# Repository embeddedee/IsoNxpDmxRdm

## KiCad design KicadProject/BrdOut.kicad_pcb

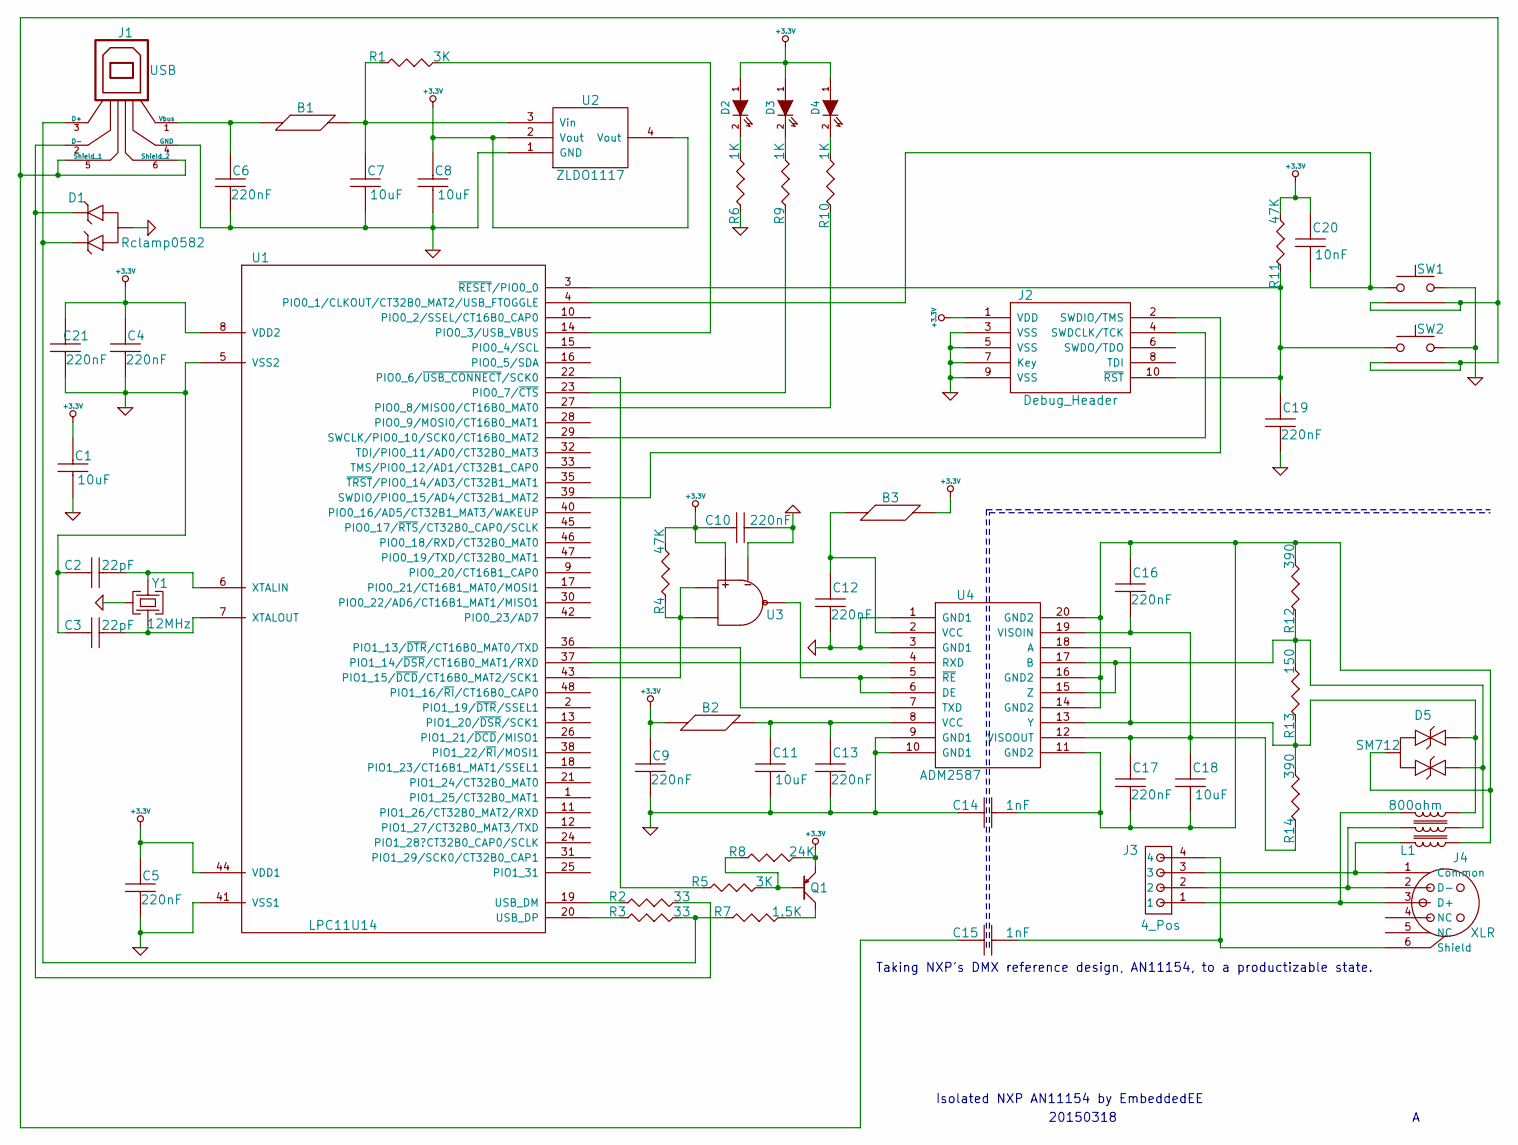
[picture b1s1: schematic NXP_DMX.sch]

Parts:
B1, B2, B3: Ferrite_Bead
C1, C7, C8, C11, C18: 10uF
C2, C3: 22pF
C4, C5, C6, C9, C10, C12, C13, C16, C17, C19, C21: 220nF
C14, C15: 1nF
C20: 10nF
D1: Rclamp0582
D2, D3, D4: LED
D5: SM712
J1: USB
J2: Debug_Header
J3: 4_Pos
J4: XLR
L1: 800ohm
Q1: BJT_PNP
R1, R5: 3K
R2, R3: 33
R4, R11: 47K
R6, R9, R10: 1K
R7: 1.5K
R8: 24K
R12, R14: 390
R13: 150
SW1, SW2: Button
U1: LPC11U14
U2: ZLDO1117
U3: 1G_NAND
U4: ADM2587
Y1: 12MHz

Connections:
+3.3V: B2.1 (B1), B3.2 (B2), C1.1 (C1), C4.1 (C1), C5.1 (C1), C8.1 (C1), C9.1 (C1), C10.1 (C1), C20.1 (C1), C21.1 (C1), D2.1 (A), D3.1 (A), D4.1 (A), J2.1 (VDD), Q1.2 (E), R4.2 (R2), R8.2 (R2), R11.2 (R2), U1.8 (VDD2), U1.44 (VDD1), U2.2 (Vout), U2.4 (Vout), U3.5 (Vcc)
GND: C1.2 (C2), C2.1 (C1), C3.1 (C1), C4.2 (C2), C5.2 (C2), C6.2 (C2), C7.2 (C2), C8.2 (C2), C9.2 (C2), C10.2 (C2), C11.2 (C2), C12.2 (C2), C13.2 (C2), C14.1 (C1), C19.2 (C2), C21.2 (C2), D1.3 (A), J1.4 (GND), J2.3 (VSS), J2.5 (VSS), J2.7 (Key), J2.9 (VSS), R6.1 (R1), SW1.2, SW2.2, U1.5 (VSS2), U1.41 (VSS1), U2.1 (GND), U3.3 (Vss), U4.1 (GND1), U4.3 (GND1), U4.9 (GND1), U4.10 (GND1), Y1.3 (Shield)
unnamed: B1.1 (B1), C6.1 (C1), J1.1 (Vbus)
unnamed: B1.2 (B2), C7.1 (C1), R1.1 (R1), U2.3 (Vin)
unnamed: B2.2 (B2), C11.1 (C1), C13.1 (C1), U4.8 (VCC)
unnamed: B3.1 (B1), C12.1 (C1), U4.2 (VCC)
unnamed: C2.2 (C2), U1.6 (XTALIN), Y1.1 (Y1)
unnamed: C3.2 (C2), U1.7 (XTALOUT), Y1.2 (Y2)
unnamed: C14.2 (C2), C16.1 (C1), C17.2 (C2), C18.2 (C2), D5.3 (A), L1.6, R12.2 (R2), U4.11 (GND2), U4.14 (GND2), U4.16 (GND2), U4.20 (GND2)
unnamed: C15.1 (C1), J1.5 (Shield_1), J1.6 (Shield_2), SW1.3, SW1.4, SW2.3, SW2.4
unnamed: C15.2 (C2), J3.4, J4.6 (Shield)
unnamed: C16.2 (C2), C17.1 (C1), C18.1 (C1), R14.1 (R1), U4.12 (VISOOUT), U4.19 (VISOIN)
unnamed: C19.1 (C1), J2.10 (~RST), R11.1 (R1), SW2.1, U1.3 (~RESET~/PIO0_0)
unnamed: C20.2 (C2), SW1.1, U1.4 (PIO0_1/CLKOUT/CT32B0_MAT2/USB_FTOGGLE)
unnamed: D1.1 (K1), J1.2 (D-), R2.2 (R2)
unnamed: D1.2 (K2), J1.3 (D+), R3.2 (R2), R7.1 (R1)
unnamed: D2.2 (K), R6.2 (R2)
unnamed: D3.2 (K), R9.2 (R2)
unnamed: D4.2 (K), R10.2 (R2)
unnamed: D5.1 (K1), L1.4, R13.1 (R1), R14.2 (R2), U4.13 (Y), U4.18 (A)
unnamed: D5.2 (K2), L1.5, R12.1 (R1), R13.2 (R2), U4.15 (Z), U4.17 (B)
unnamed: J2.2 (SWDIO/TMS), U1.39 (SWDIO/PIO0_15/AD4/CT32B1_MAT2)
unnamed: J2.4 (SWDCLK/TCK), U1.29 (SWCLK/PIO0_10/SCK0/CT16B0_MAT2)
unnamed: J3.1, J4.3 (D+), L1.3
unnamed: J3.2, J4.2 (D-), L1.2
unnamed: J3.3, J4.1 (Common), L1.1
unnamed: Q1.1 (B), R5.2 (R2), R8.1 (R1)
unnamed: Q1.3 (C), R7.2 (R2)
unnamed: R1.2 (R2), U1.14 (PIO0_3/USB_VBUS)
unnamed: R2.1 (R1), U1.19 (USB_DM)
unnamed: R3.1 (R1), U1.20 (USB_DP)
unnamed: R4.1 (R1), U1.43 (PIO1_15/~DCD~/CT16B0_MAT2/SCK1), U3.1 (In1), U3.2 (In2)
unnamed: R5.1 (R1), U1.22 (PIO0_6/~USB_CONNECT~/SCK0)
unnamed: R9.1 (R1), U1.23 (PIO0_7/~CTS)
unnamed: R10.1 (R1), U1.27 (PIO0_8/MISO0/CT16B0_MAT0)
unnamed: U1.36 (PIO1_13/~DTR~/CT16B0_MAT0/TXD), U4.7 (TXD)
unnamed: U1.37 (PIO1_14/~DSR~/CT16B0_MAT1/RXD), U4.4 (RXD)
unnamed: U3.4 (Out), U4.5 (~RE), U4.6 (DE)

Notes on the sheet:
20150318
Taking NXP's DMX reference design, AN11154, to a productizable state.
Isolated NXP AN11154 by EmbeddedEE

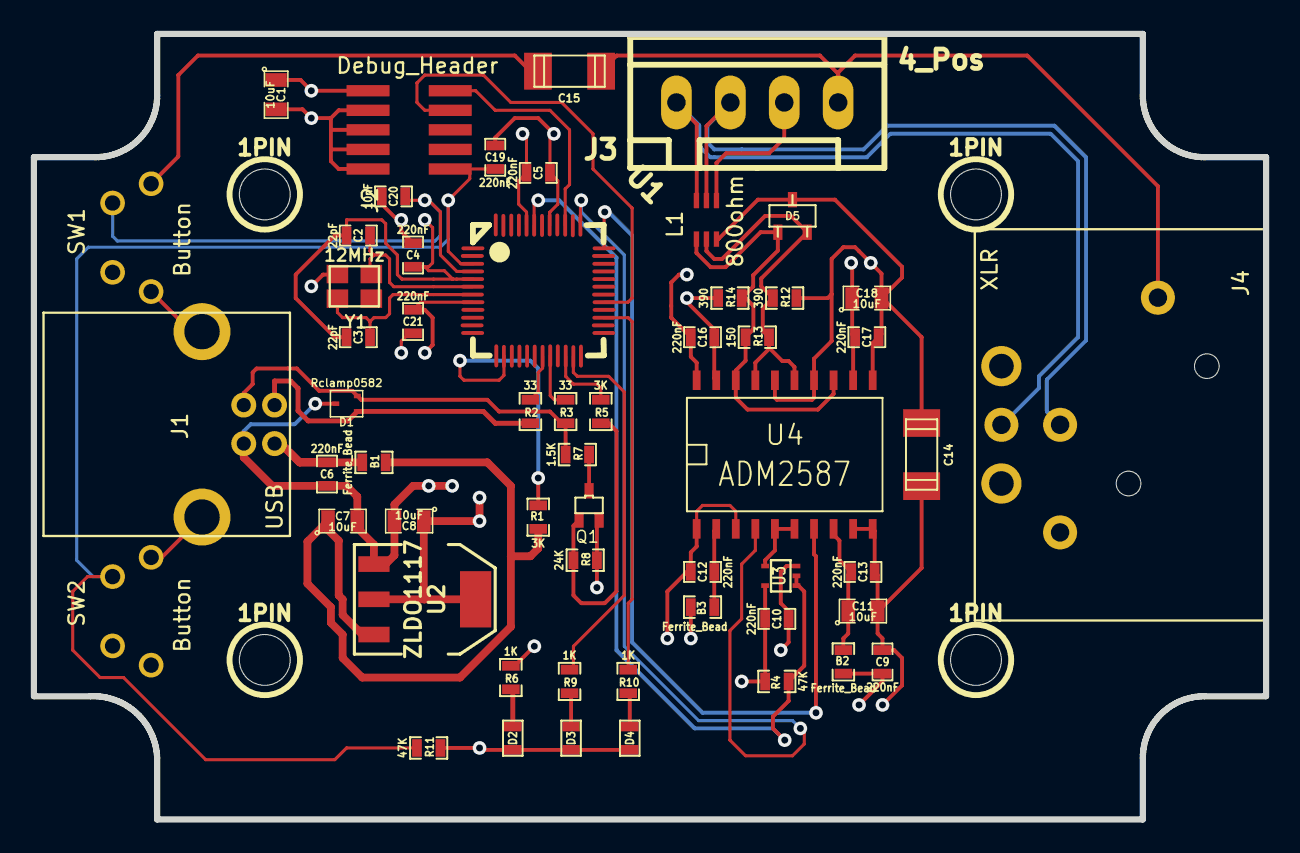
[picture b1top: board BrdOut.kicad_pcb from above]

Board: 4 copper layers, 80.0 x 51.0 mm, 60 parts (0 on the bottom side), 38 nets.

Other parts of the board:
1PIN, 1PIN#2, 1PIN#3, 1PIN#4: P***; 1pin

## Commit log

2015-04-03 Add starting version of all files.
2015-04-09 Add label to schematic
2015-05-09 Add missing ground connection on ADM2587.
